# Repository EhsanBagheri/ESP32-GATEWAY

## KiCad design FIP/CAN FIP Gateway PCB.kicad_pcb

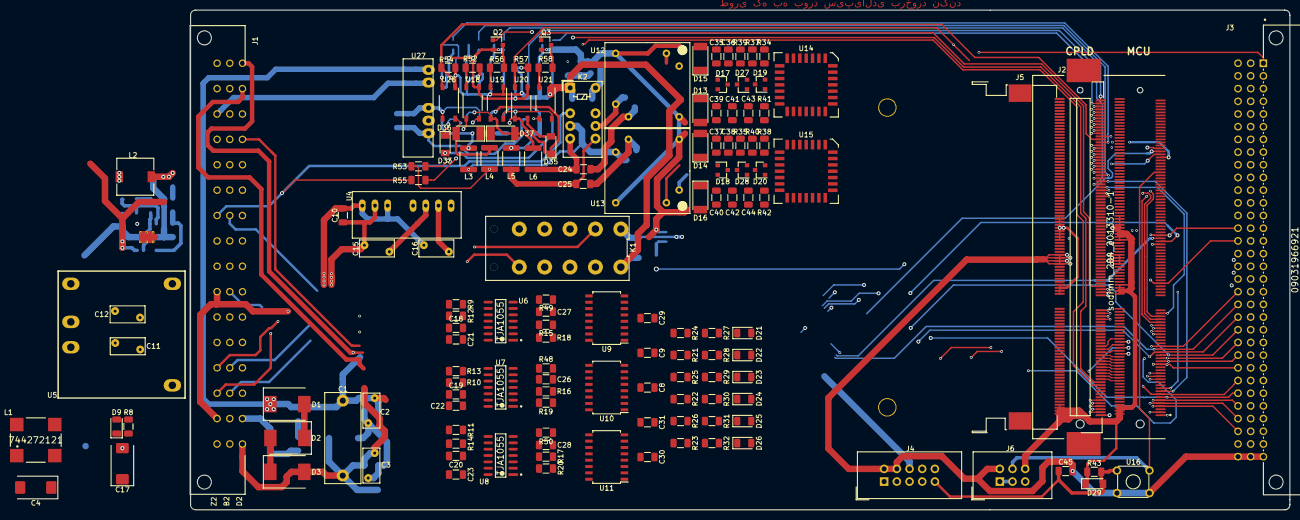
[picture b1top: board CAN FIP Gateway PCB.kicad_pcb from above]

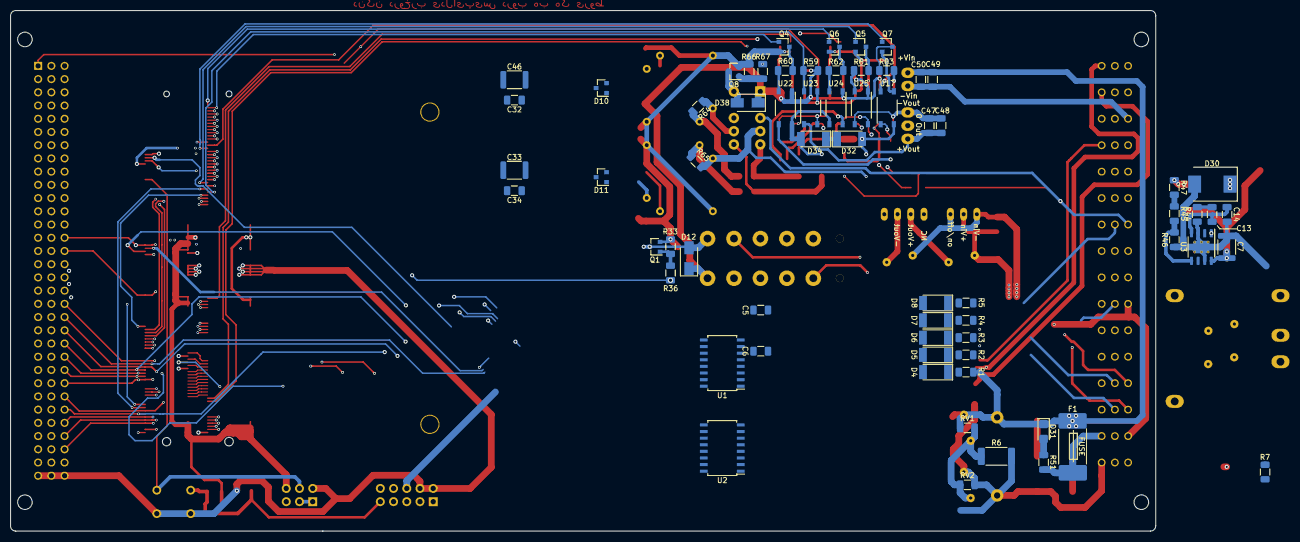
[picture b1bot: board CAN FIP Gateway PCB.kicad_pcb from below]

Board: 4 copper layers, 220.0 x 100.0 mm, 208 parts (66 on the bottom side), 239 nets.

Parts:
C1: 10nF-500V.mkt; C_Rect_L18.0mm_W7.0mm_P15.00mm_FKS3_FKP3
C2, C3: 4.7nF-2kV; RV_Disc_D7mm_W3.4mm_P5mm
C4: Tantal_47UF_50V(D); CP_EIA-7343-31_Kemet-D
C5, C19, C20, C26, C27, C28, C29, C31, C38: 100n(1206); C_1206_3216Metric
C6, C8, C9, C18, C30, C32, C34, C36, C48, C50: 100n(1206)#; C_1206_3216Metric
C7, C33, C46: 10uf-1812; C_1812_4532Metric
C10: 4.7uF(1206)50V; R_1206_3216Metric
C11, C12, C15, C16: 1nF-2kV; RV_Disc_D7mm_W3.4mm_P5mm
C13: 22nf(1206)#; C_1206_3216Metric
C14: 220pF(1206); C_1206_3216Metric
C17: Tantal_100UF_16V(D); CP_EIA-7343-31_Kemet-D
C21, C22, C23: 4n7F(1206); R_1206_3216Metric
C24, C25: 470nF(1206); C_1206_3216Metric
C35, C37: 1uf(1206); C_1206_3216Metric
C39, C40: 3.3nF(1206); C_1206_3216Metric
C41, C42: 47pF(1206); C_1206_3216Metric
C43, C44: 100pF(1206); C_1206_3216Metric
C45: 1uf(1206)#; C_1206_3216Metric
C47, C49: 10uF(1206); C_1206_3216Metric
D1, D2, D3: TVS11V3000W; D_SMC
D4, D5, D6, D7, D8: 5.1v_z_MELF; D_MELF
D9: LEDGreen(1206); LED_1206_3216Metric
D10, D11, D17, D18, D19, D20, D27, D28: BAV99; SOT-23
D12, D38: P4SMA10CA; D_SMA
D13, D14, D15, D16: Z4.7V-Melf; D_MELF
D21, D23, D25: LEDYellow(1206); LED_1206_3216Metric
D22, D24, D26: LEDBlue(1206); LED_1206_3216Metric
D29, D33, D35: 1N4148; D_MiniMELF
D30: SS34-smc; D_SMC
D31: LED_RED(1206); LED_1206_3216Metric_Castellated
D32, D34, D36, D37: zener.60v.melf; D_MELF
F1: Fuse1808Holder; fuse.holder.1808
J1: DIN-Power_F048MS-3,0C1-2; 09061486901
J2: sodimm_204_2013310-1; sodimm204pinTE-2013310-1-0
J3: 09031966921; Harting-09031966921-0-0-0
J4: IDC_box_2*5_straight; IDC-Header_2x05_P2.54mm_Vertical
J5: AS0A626-U2SN-7F; FOXCONN_AS0A626-U2SN-7F
J6: IDC_BOX_02x03_vertical; IDC-Header_2x03_P2.54mm_Vertical
K1: S4-5V; Panasonic-S4-5V
K2: FINDER-30.22; Relay_DPDT_Omron_G6S-2
L1: 744272121; Wurth_Electronics-744272121-Manufacturer_Recommended
L2: 22uh-smd7*7; L_7.3x7.3
L3, L4, L5, L6: 1mH(1812); L_1812_4532Metric
LOGO1: MantisModule9.2; mantis_module
Q1, Q2, Q3, Q4, Q5, Q6, Q7, Q8: BC817_sot23; SOT-23
R1, R53, R55: 100k(1206)#; R_1206_3216Metric
R2, R3, R4, R5: 100k(1206); R_1206_3216Metric
R6: 1M(2512); R_2512_6332Metric
R7, R15, R16, R17, R24, R25, R26, R33, R43, R52, R54, R57, R59, R66: 10K(1206); R_1206_3216Metric
R8: 330R(1206); R_1206_3216Metric
R9, R10, R11, R12, R13, R14, R64, R65: 120R(1206); R_1206_3216Metric
R18, R19, R20: 220(1206); R_1206_3216Metric
R21, R22, R23, R27, R28, R29, R30, R31, R32: 750(1206); R_1206_3216Metric
R34, R35: 2.4R-1%(1206); R_1206_3216Metric
R36, R56, R58, R60, R61, R62, R63, R67: 1k(1206); R_1206_3216Metric
R37, R38: 39R-1%(1206); R_1206_3216Metric
R39, R40: 6.2k-1%(1206); R_1206_3216Metric
R41, R42, R47: 820R(1206); R_1206_3216Metric
R44, R51: 4.7k(1206)#; R_1206_3216Metric
R45: 8.2k1%(1206)#; R_1206_3216Metric
R46: 3.3K(1206)#; R_1206_3216Metric
R48, R49, R50: 0R(1206); R_1206_3216Metric
RV1, RV2: Varistor; R_1206_3216Metric
U1, U2, U9, U10, U11: Si8662BB-AU; SOIC-16W_5.3x10.2mm_P1.27mm
U3: L5973D; HSOP-8-1EP_3.9x4.9mm_P1.27mm_EP2.41x3.1mm_ThermalVias
U4: MCWI03-24s05; MCWI03-single
U5: MJW10-24S05; MJWI10-48S15
U6, U7, U8: TJA1055; NXP_Semiconductors-SOT108-1-12_2018-0-IPC_B
U12, U13: FieldTRS
U14, U15: FieldDRV; PLCC-28
U16: Tact_Switch_6*6mm; SW_TH_Tactile_Omron_B3F-10xx
U17, U19, U20, U21, U22, U23, U24, U25, U26: TLP181; MFSOP6-4_4.4x3.6mm_P1.27mm
U18: TLP120; MFSOP6-4_4.4x3.6mm_P1.27mm
U27: A2424S-1WR3

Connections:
17ConnA1: J1.Z20, K2.11, R55.2
17ConnB2: J1.D20, K2.12, L3.1, R65.2, U13.5
18ConnA1: J1.D18, K2.22, L4.2, R53.2, R64.1, U12.3
18ConnB2: J1.D16, K2.21
+5P: C5.1, C6.1, J1.B12, L2.2, R47.1, U1.1, U2.1
+5V: C8.1, C9.1, C11.1, C17.1, C29.1, C30.1, C31.1, C32.1, C33.1, C34.1, C46.1, D9.2, D12.1, D21.2, D22.2, D23.2, D24.2, D25.2, D26.2, D29.1, D38.1, J2.2, J2.4, J2.6, J2.8, J2.74, J2.76, J2.78, J2.80, J2.110, J2.112, J2.114, J2.116, J2.118, J2.120, J2.122, J2.124, J2.126, J3.4, J4.6, J5.2, J5.4, J5.6, J5.8, J5.74, J5.76, J5.78, J5.80, J5.110, J5.112, J5.114, J5.116, J5.118, J5.120, J5.122, J5.124, J5.126, J6.6, K1.12, K2.A1, R7.1, R24.1, R25.1, R26.1, R34.1, R35.1, R37.1, R38.1, R39.1, R40.1, R43.2, R52.1, R54.2, R57.2, R59.1, U1.16, U2.16, U5.3, U9.1, U10.1, U11.1, U14.6, U14.11, U15.6, U15.11, U19.1, U21.1, U22.1, U24.1, U25.1, U26.1
+5VL: C20.1, C23.1, C28.1, J1.D30, R17.1, U8.1, U8.10, U8.14, U11.16
+5VP: C15.1, C18.1, C19.1, C21.1, C22.1, C26.1, C27.1, R15.1, R16.1, U4.6, U6.1, U6.10, U6.14, U7.1, U7.10, U7.14, U9.16, U10.16
+24V: C10.1, C11.2, C15.2, L1.3, U4.2, U5.1, U5.6
+BATT: C1.1, C2.1, C4.1, C7.1, C49.1, C50.1, D1.1, D31.1, F1.1, L1.4, R1.2, RV1.1, U3.8, U27.1
-BATT: C1.2, C3.2, C4.2, C5.2, C6.2, C7.2, C14.2, C49.2, C50.2, D3.2, D4.2, D5.2, D6.2, D7.2, D8.2, D30.2, J1.D2, J1.Z28, L1.1, R6.2, R44.2, R46.2, RV2.2, U1.8, U2.4, U2.5, U2.8, U3.3, U3.7, U3.9, U27.2
BoardID: J1.B22, U2.2
CPLD_MODE-TMS: J4.3, J5.5
CPLD_SCLK-TCK: J4.1, J5.3
CPLD_SDI-TDI: J4.5, J5.7
CPLD_SDO-TDO: J4.7, J5.9
CPLD_TRST: C45.1, D29.2, J4.9, J5.1, R43.1, U16.1
CPLD_ispEN-Prog: J4.10, J5.11
E_BT_UM1A: J1.B6, R2.2
E_BT_UM1B: J1.B14, R4.2
E_BT_UM2A: J1.B20, R5.2
E_BT_UM2B: J1.B8, R3.2
Earth: C2.2, C3.1, R6.1, RV1.2, RV2.1
FIP1CDn: J5.193, U14.5
FIP1RESETn: J5.199, U14.9
FIP1RxD: J5.191, U14.4
FIP1TS0: J5.183, U14.27
FIP1TS1: J5.181, U14.26
FIP1TxCK: J5.187, U14.2
FIP1TxD: J5.185, U14.1, U14.28
FIP1TxEn: J5.197, U14.8
FIP1TxEr: J5.189, U14.3
FIP1WDGn: J5.195, U14.7
FIP2CDn: J5.167, U15.5
FIP2RESETn: J5.173, U15.9
FIP2RxD: J5.165, U15.4
FIP2TS0: J5.157, U15.27
FIP2TS1: J5.155, U15.26
FIP2TxCK: J5.161, U15.2
FIP2TxD: J5.159, U15.1, U15.28
FIP2TxEn: J5.171, U15.8
FIP2TxEr: J5.163, U15.3
FIP2WDGn: J5.169, U15.7
FIPOpto1Out: J5.21, R52.2, U18.6
FIPOpto2CMD: J5.23, Q2.1
FIPOpto3CMD: J5.79, Q3.1
FIPOpto4Out: J5.147, R59.2, U23.6
FIPOpto5CMD: J5.153, Q5.1
FIPOpto6CMD: J5.175, Q7.1
FIPOpto7Out: J5.177, R54.1, U17.6
FIPOpto8Out: J5.179, R57.1, U20.6
FIPOpto9CMD: J5.201, Q4.1
FIPOpto10CMD: J5.203, Q6.1
FIPRelayCMD: J2.1, R67.2
FIPRelayFB: D38.2, J2.3, K2.A2, Q8.3
GND: C8.2, C9.2, C12.1, C17.2, C29.2, C30.2, C31.2, C32.2, C33.2, C34.2, C35.2, C36.2, C37.2, C38.2, C45.2, C46.2, D13.2, D14.2, D15.2, D16.2, J2.94, J2.96, J2.98, J2.100, J3.94, J3.95, J3.96, J4.2, J4.4, J5.94, J5.96, J5.98, J5.100, J6.2, Q1.2, Q2.2, Q3.2, Q4.2, Q5.2, Q6.2, Q7.2, Q8.2, R7.2, R8.2, R33.2, R66.2, U1.9, U2.9, U2.10, U2.11, U5.5, U9.8, U10.8, U11.8, U12.7, U12.8, U13.7, U13.8, U14.21, U14.25, U15.21, U15.25, U16.3, U16.4, U17.4, U18.4, U20.4, U23.4
GNDA: C16.1, C18.2, C19.2, C21.2, C22.2, C26.2, C27.2, J1.Z4, J1.Z14, R48.2, R49.2, U4.7, U6.13, U7.13, U9.9, U10.9
GNDPWR: C10.2, C12.2, C16.2, L1.2, U4.1, U4.3, U5.2
GNDS: C20.2, C23.2, C28.2, J1.D32, R50.2, U8.13, U11.9
InputsupplyOK: J3.1, U2.14
IsolatedBoardID: J2.111, U2.15
MCU-Pin89: J2.24, J5.25
MCU-Pin90: J2.26, J5.27
MCU-Pin91: J2.28, J5.29
MCU-Pin92: J2.30, J5.31
MCU-Pin93: J2.32, J5.33
MCU-Pin94: J2.34, J5.35
MCU-Pin95: J2.36, J5.37
MCU-Pin96: J2.38, J5.39
MCU-Pin97: J2.40, J5.41
MCU-Pin99: J2.44, J5.43
MCU-Pin101: J2.48, J5.45
MCU-Pin103: J2.52, J5.47
MCU_BKGD: J2.108, J6.1, J6.3
MCU_RST: J2.155, J6.4, U16.2
unnamed: C13.1, C14.1, U3.4
unnamed: C13.2, R44.1
unnamed: C24.1, R64.2, U12.5
unnamed: C24.2, K2.14, L6.2
unnamed: C25.1, R65.1, U13.3
unnamed: C25.2, K2.24, L5.1
unnamed: C35.1, C36.1, U14.10
unnamed: C37.1, C38.1, U15.10
unnamed: C39.1, U14.20
unnamed: C39.2, U14.19
unnamed: C40.1, U15.20
unnamed: C40.2, U15.19
unnamed: C41.1, C43.1, U14.23
unnamed: C41.2, U14.22
unnamed: C42.1, C44.1, U15.23
unnamed: C42.2, U15.22
unnamed: C43.2, R41.2
unnamed: C44.2, R42.2
unnamed: C47.1, C48.1, U23.1, U27.6
unnamed: C47.2, C48.2, U25.4, U26.4, U27.4
unnamed: D1.2, D2.1
unnamed: D2.2, D3.1
unnamed: D4.1, R1.1, U2.3
unnamed: D5.1, R2.1, U1.2
unnamed: D6.1, R3.1, U1.3
unnamed: D7.1, R4.1, U1.4
unnamed: D8.1, R5.1, U1.5
unnamed: D9.1, R8.1
unnamed: D10.1, D17.2, D19.3, U12.2, U14.18
unnamed: D10.2, D17.1, D27.3, U12.6, U14.12
unnamed: D10.3, D13.1
unnamed: D11.1, D18.2, D20.3, U13.2, U15.18
unnamed: D11.2, D18.1, D28.3, U13.6, U15.12
unnamed: D11.3, D14.1
unnamed: D15.1, D17.3
unnamed: D16.1, D18.3
unnamed: D19.1, U14.17
unnamed: D19.2, U14.16
unnamed: D20.1, U15.17
unnamed: D20.2, U15.16
unnamed: D21.1, R27.2
unnamed: D22.1, R28.2
unnamed: D23.1, R29.2
unnamed: D24.1, R30.2
unnamed: D25.1, R31.2
unnamed: D26.1, R32.2
unnamed: D27.1, U14.13
unnamed: D27.2, U14.14
unnamed: D28.1, U15.13
unnamed: D28.2, U15.14
unnamed: D30.1, L2.1, U3.1
unnamed: D31.2, R51.1
unnamed: D32.1, D34.1
unnamed: D32.2, L3.2, U17.3, U20.1
unnamed: D33.1, U17.1
unnamed: D33.2, U22.4
unnamed: D34.2, L5.2, U22.6, U24.4
unnamed: D35.1, U24.6
unnamed: D35.2, U20.3
unnamed: D36.1, D37.1
unnamed: D36.2, L4.1, U21.4, U26.6
unnamed: D37.2, L6.1, U19.4, U25.6
unnamed: F1.2, J1.D4, R51.2
unnamed: Q1.1, R33.1, R36.1
unnamed: Q2.3, R56.1
unnamed: Q3.3, R58.1
unnamed: Q4.3, R60.2
unnamed: Q5.3, R61.1
unnamed: Q6.3, R62.2
unnamed: Q7.3, R63.1
unnamed: Q8.1, R66.1, R67.1
unnamed: R9.1, U6.8
unnamed: R10.1, U7.8
unnamed: R11.1, U8.8
unnamed: R12.2, U6.9
unnamed: R13.2, U7.9
unnamed: R14.2, U8.9
unnamed: R15.2, U6.3, U9.10
unnamed: R16.2, U7.3, U10.10
unnamed: R17.2, U8.3, U11.10
unnamed: R18.1, U6.2
unnamed: R18.2, U9.13
unnamed: R19.1, U7.2
unnamed: R19.2, U10.13
unnamed: R20.1, U8.2
unnamed: R20.2, U11.13
unnamed: R21.1, U9.4
unnamed: R22.1, U10.4
unnamed: R23.1, U11.4
unnamed: R34.2, R37.2, R39.2, U14.15
unnamed: R35.2, R38.2, R40.2, U15.15
unnamed: R41.1, U14.24
unnamed: R42.1, U15.24
unnamed: R45.1, R47.2
unnamed: R45.2, R46.1, U3.5
unnamed: R48.1, U7.7
unnamed: R49.1, U6.7
unnamed: R50.1, U8.7
unnamed: R53.1, U18.1
unnamed: R55.1, U18.3
unnamed: R56.2, U19.3
unnamed: R58.2, U21.3
unnamed: R60.1, U22.3
unnamed: R61.2, U25.3
unnamed: R62.1, U24.3
unnamed: R63.2, U26.3
unnamed: U6.4, U9.11
unnamed: U6.5, U9.12
unnamed: U6.6, U9.14
unnamed: U7.4, U10.11
unnamed: U7.5, U10.12
unnamed: U7.6, U10.14
unnamed: U8.4, U11.11
unnamed: U8.5, U11.12
unnamed: U8.6, U11.14
unnamed: U19.6, U21.6, U23.3
RelayedTrainLineACANH: J1.Z16, K1.4
RelayedTrainLineACANL: J1.Z18, K1.10
RelayedTrainLineBCANH: J1.Z6, K1.2
RelayedTrainLineBCANL: J1.Z8, K1.8
RxD0: J2.17, J5.149
Spi0-MISO: J2.25, J5.65
Spi0-MOSI: J2.27, J5.67
Spi0-SCK: J2.29, J5.69
Spi1-MISO: J2.69, J5.145
Spi1-MOSI: J2.67, J5.143
Spi1-SCK: J2.65, J5.141
Spi1-~CS: J2.63, J5.139
Spi2-MISO: J2.61, J5.77
Spi2-MOSI: J2.59, J5.75
Spi2-SCK: J2.57, J5.73
Spi2-~CS: J2.55, J5.71
TrainLine1CRx0: J2.15, J3.78, R24.2, R27.1, U9.7
TrainLine1CTx0: J2.13, J3.81, R21.2, R28.1
TrainLine1EN: J2.11, J3.84, U9.3
TrainLine1~ERR: J2.7, J3.90, U9.6
TrainLine1~STB: J2.9, J3.87, U9.5
TrainLine2CRx0: J2.43, J3.63, R25.2, R29.1, U10.7
TrainLine2CTx0: J2.41, J3.66, R22.2, R30.1
TrainLine2EN: J2.39, J3.69, U10.3
TrainLine2~ERR: J2.35, J3.75, U10.6
TrainLine2~STB: J2.37, J3.72, U10.5
TrainLineACANH: K1.5, R9.2, U6.11
TrainLineACANL: K1.11, R12.1, U6.12
TrainLineBCANH: K1.3, R10.2, U7.11
TrainLineBCANL: K1.9, R13.1, U7.12
TrainLineRelayCMD: J2.113, J3.42, R36.2
TrainLineRelayFB: D12.2, J2.81, J3.45, K1.1, Q1.3
TxD0: J2.19, J5.151
isolatedE_BT_UM1A: J2.169, U1.15
isolatedE_BT_UM1B: J2.107, U1.13
isolatedE_BT_UM2A: J2.109, U1.12
isolatedE_BT_UM2B: J2.171, U1.14
isolatedoutrsrv1: J1.B32, U1.6
isolatedoutrsrv2: J1.B30, U1.7
outrsrv1: J2.165, U1.11
outrsrv2: J2.167, U1.10
sysCANH: J1.D24, R11.2, U8.11
sysCANL: J1.D26, R14.1, U8.12
sysCRx0: J2.47, J3.57, R26.2, R31.1, U11.7
sysCTx0: J2.45, J3.60, R23.2, R32.1
sysEN: J2.50, J3.49, U11.3
sys~ERR: J2.42, J3.52, U11.6
sys~STB: J2.46, J3.46, U11.5
